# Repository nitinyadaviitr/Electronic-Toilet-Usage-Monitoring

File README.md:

# Electronic-Toilet-Usage-Monitoring
For accelerating the effectiveness of Swachh Bharat Abhiyaan, the monitoring of the goals under Swachh Bharat Abhiyaan is the most important thing to be done.
To successfully implement the cause of the Millions of toilets made under Swachh Bharat Abhiyaan, having a record of how much they are actually being used is important.
For monitoring toilet usage in the rural areas of India, we have developed ETUM. 
ETUM has been made considering conditions like lack of electricity in villages, remoteness of the area and lack of services.
ETUM is a cost effective device which will tell the approximate usage of the toilets for a duration of about 5 months after which the data will have to be recorded manually.

General Description:-
ETUM operates on the principle of human detection technology using a PIR sensor. A PIR sensor detects Infrared rays emitted by the human body.
Everytime a person enters into the toilet, the PIR sensor will read high increasing the previous value by 1, and will store this data for about 5 months with average usage in every week during these
months.
Our idea suggests that the device will be installed in every toilet present into the village and after a duration of 5 months a person has to go to every house and take
the reading of the device and replace the battery used in it. Then he will give the feedback to a centralised database where the data of all the villages will be recorded and studied.
The device is accurate as whole device works without manual work (except manual recording) and has a long lifetime if not damaged physically.

Cost-effectiveness:-
Calculating the whole manufacturing of the device along with the price of each and every component used in it, the device will have an estimated cost of 150 rupees.
The exact cost of the device depends on the amount of quantities being ordered collectively and from where they are being ordered and many other factors.
(The price data of products we have considered for evaluation of cost of our device have been provided in the PDF attached)

Scalability:-
The device is safe to use and have an optimum cost for a large scale usage in rural or urban areas.
The device has no maintenance cost and low operating cost.
Also assigning the responsibility of data recording from every house in the village to a person is feasible and would help to keep an accurate record of the whole data.
Extremely low maintenance cost, long lifetime and low cost of the device makes it perfect for large scale usage.

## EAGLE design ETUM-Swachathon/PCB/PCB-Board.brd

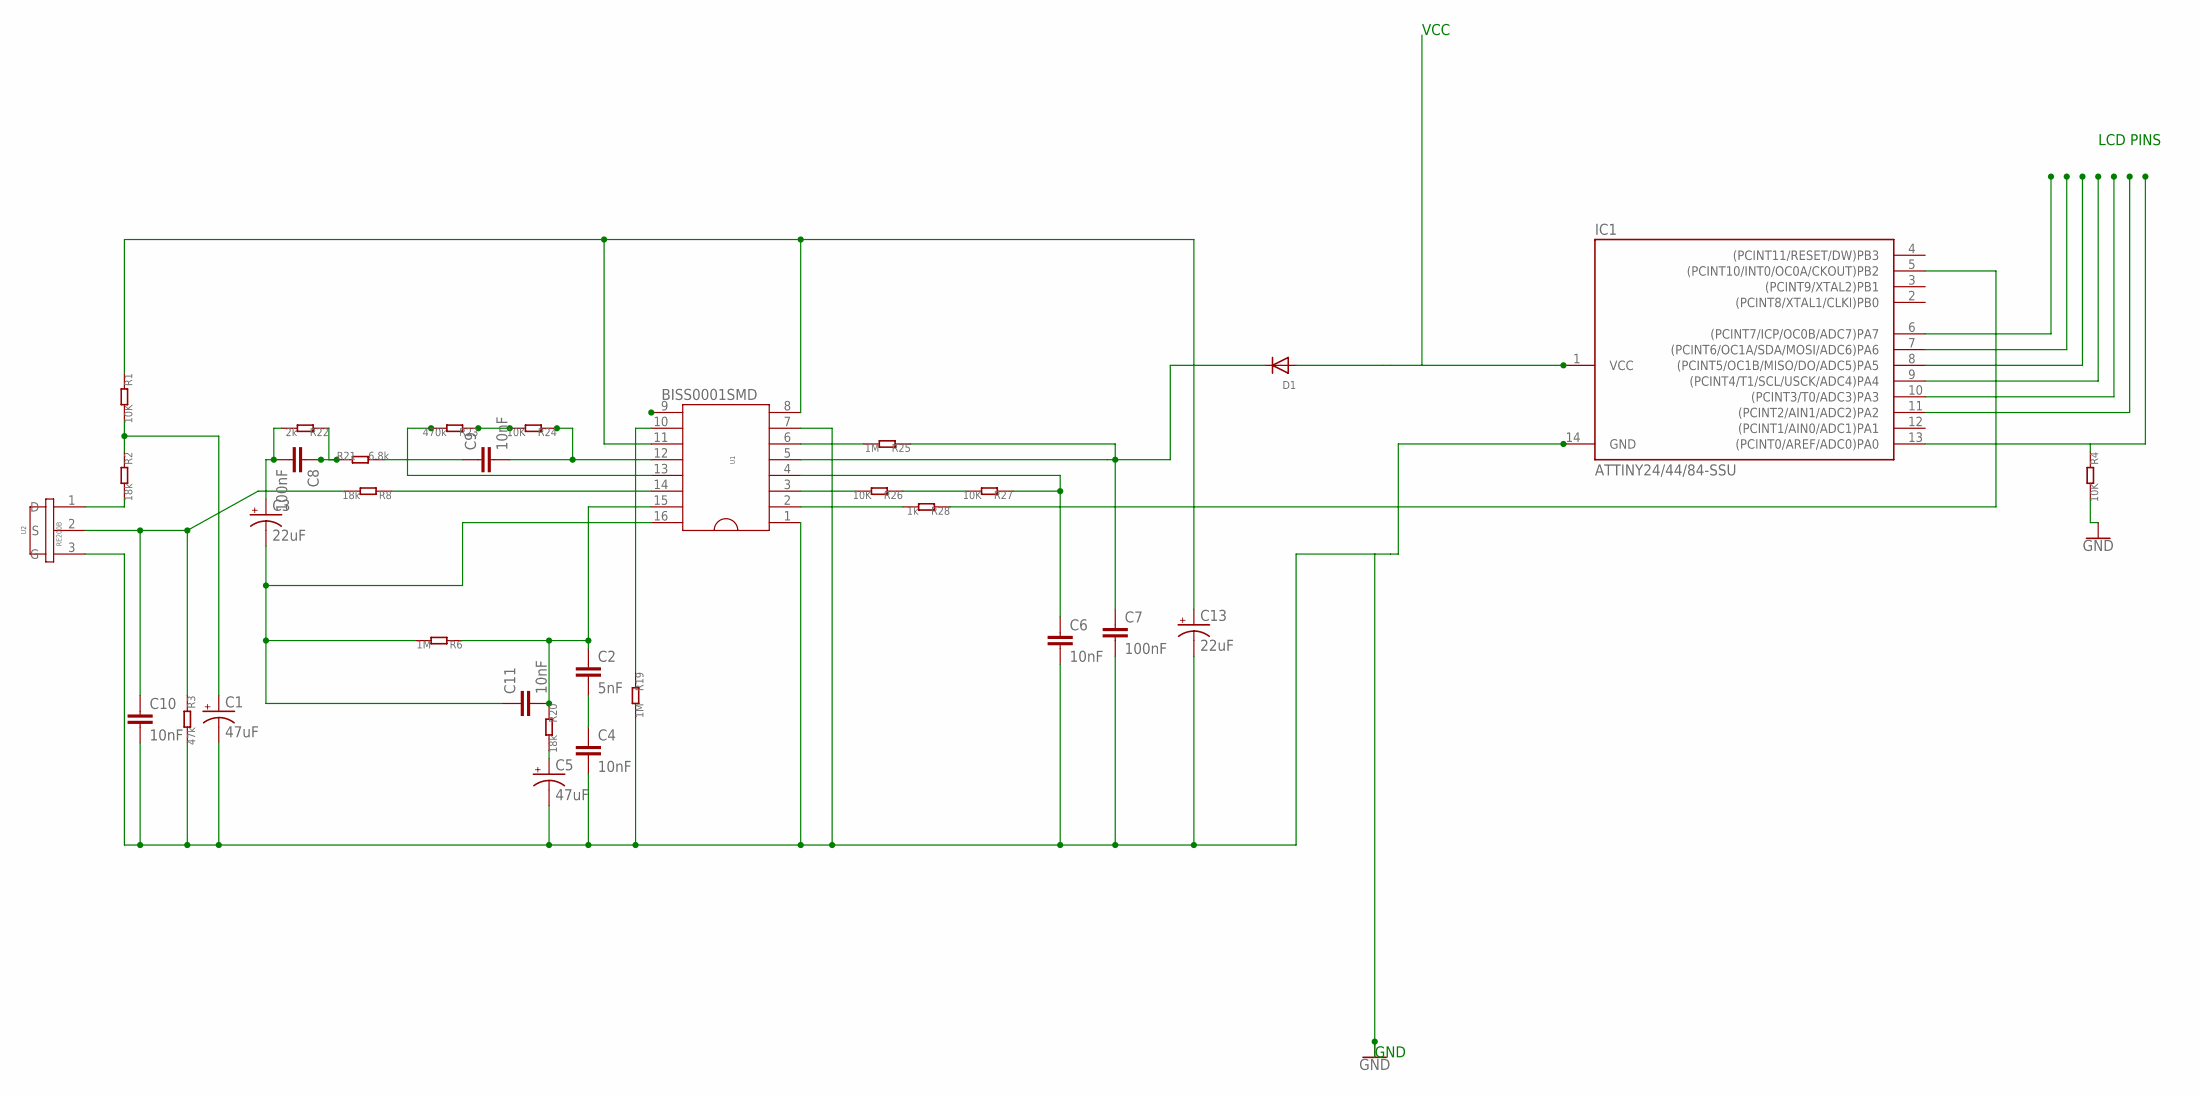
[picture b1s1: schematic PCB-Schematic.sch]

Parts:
C1, C5: 47uF; 085CS_1W
C2: 5nF; C0805
C3, C13: 22uF; 085CS_1W
C4, C6, C9, C10, C11: 10nF; C0805
C7, C8: 100nF; C0805
D1: DIODESOD-323F; SOD-323F
IC1: ATTINY24/44/84-SSU; SOIC14
R1, R4, R24, R26, R27: 10K; R0603
R2, R8, R20: 18k; R0603
R3: 47k; R0603
R6, R19, R25: 1M; R0603
R21: 6.8k; R0603
R22: 2k; R0603
R23: 470k; R0603
R28: 1k; R0603
U1: BISS0001SMD; SOP16
U2: RE200B

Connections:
GND: C1.-, C4.2, C5.-, C6.2, C7.2, C10.2, C13.-, IC1.14 (GND), R3.2, R4.2, R19.2, U1.1, U1.7, U2.3 (G)
unnamed: R2.2, U2.1 (D)
unnamed: C1.+, R1.2, R2.1
unnamed: R19.1, U1.10
unnamed: R23.2, U1.13
unnamed: R8.1, U1.14
unnamed: C10.1, R3.1, R8.2, U2.2 (S)
unnamed: C3.-, C11.1, R6.2, U1.16
unnamed: C8.1, R21.1, R22.1
unnamed: C9.1, R21.2
unnamed: C5.+, R20.2
unnamed: C2.1, C11.2, R6.1, R20.1, U1.15
unnamed: C2.2, C4.1
unnamed: R25.2, U1.6
unnamed: R23.1, R24.2
unnamed: C6.1, R27.1, U1.4
unnamed: R26.2, U1.3
unnamed: C7.1, D1.C, R25.1, U1.5
unnamed: C9.2, R24.1, U1.12
unnamed: R28.2, U1.2
unnamed: R26.1, R27.2
unnamed: IC1.5 ((PCINT10/INT0/OC0A/CKOUT)PB2), R28.1
unnamed: C13.+, R1.1, U1.8, U1.11
unnamed: C3.+, C8.2, R22.2
unnamed: D1.A, IC1.1 (VCC)
unnamed: IC1.13 ((PCINT0/AREF/ADC0)PA0), R4.1

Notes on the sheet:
VCC
GND
LCD PINS

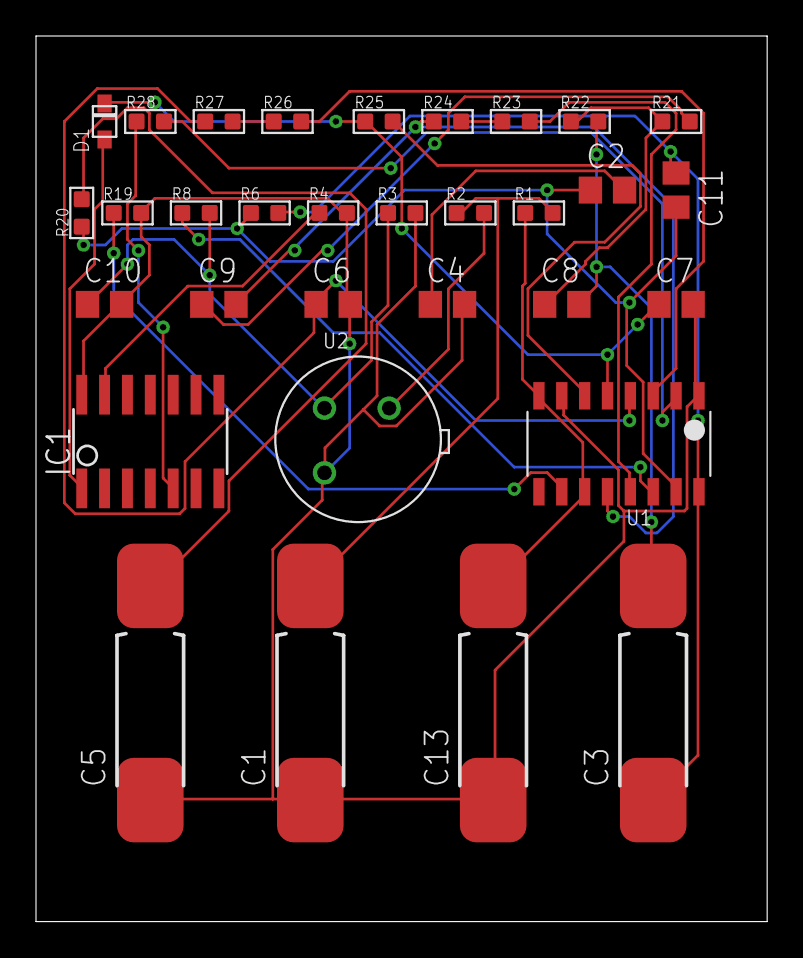
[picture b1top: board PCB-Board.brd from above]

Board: 2 copper layers, 40.6 x 49.2 mm, 32 parts (0 on the bottom side), 26 nets.

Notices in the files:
parts and their libraries:
SparkFun-PowerSymbols: Licensing: Creative Commons ShareAlike 4.0 International - https://creativecommons.org/licenses/by-sa/4.0
